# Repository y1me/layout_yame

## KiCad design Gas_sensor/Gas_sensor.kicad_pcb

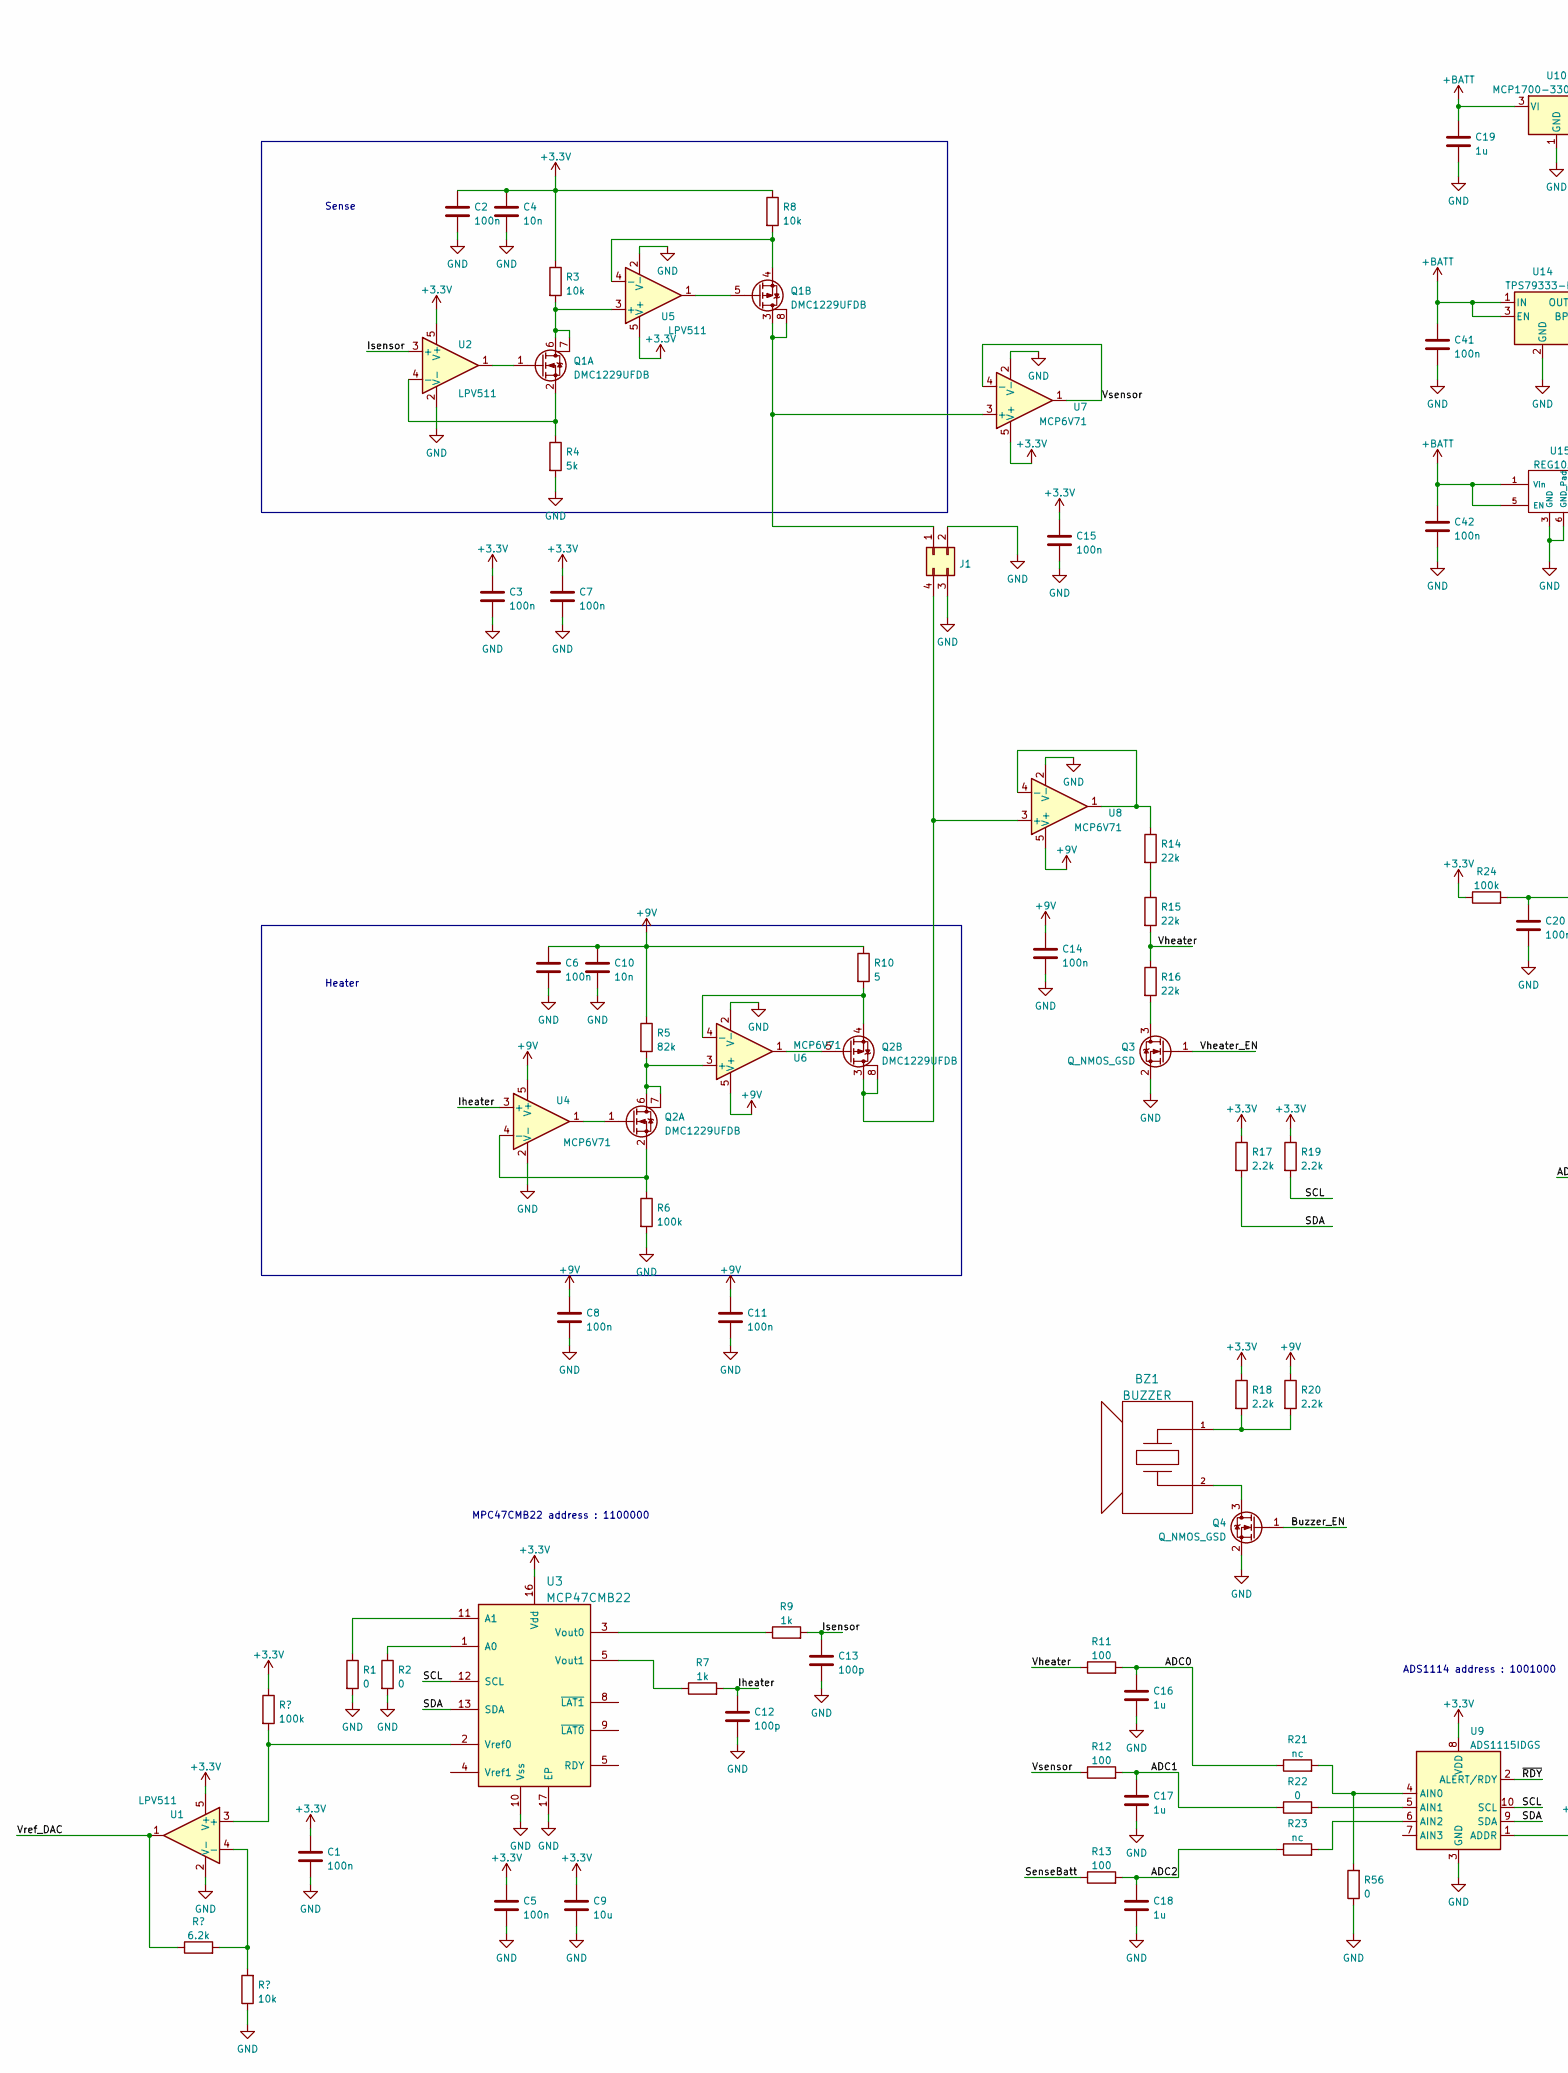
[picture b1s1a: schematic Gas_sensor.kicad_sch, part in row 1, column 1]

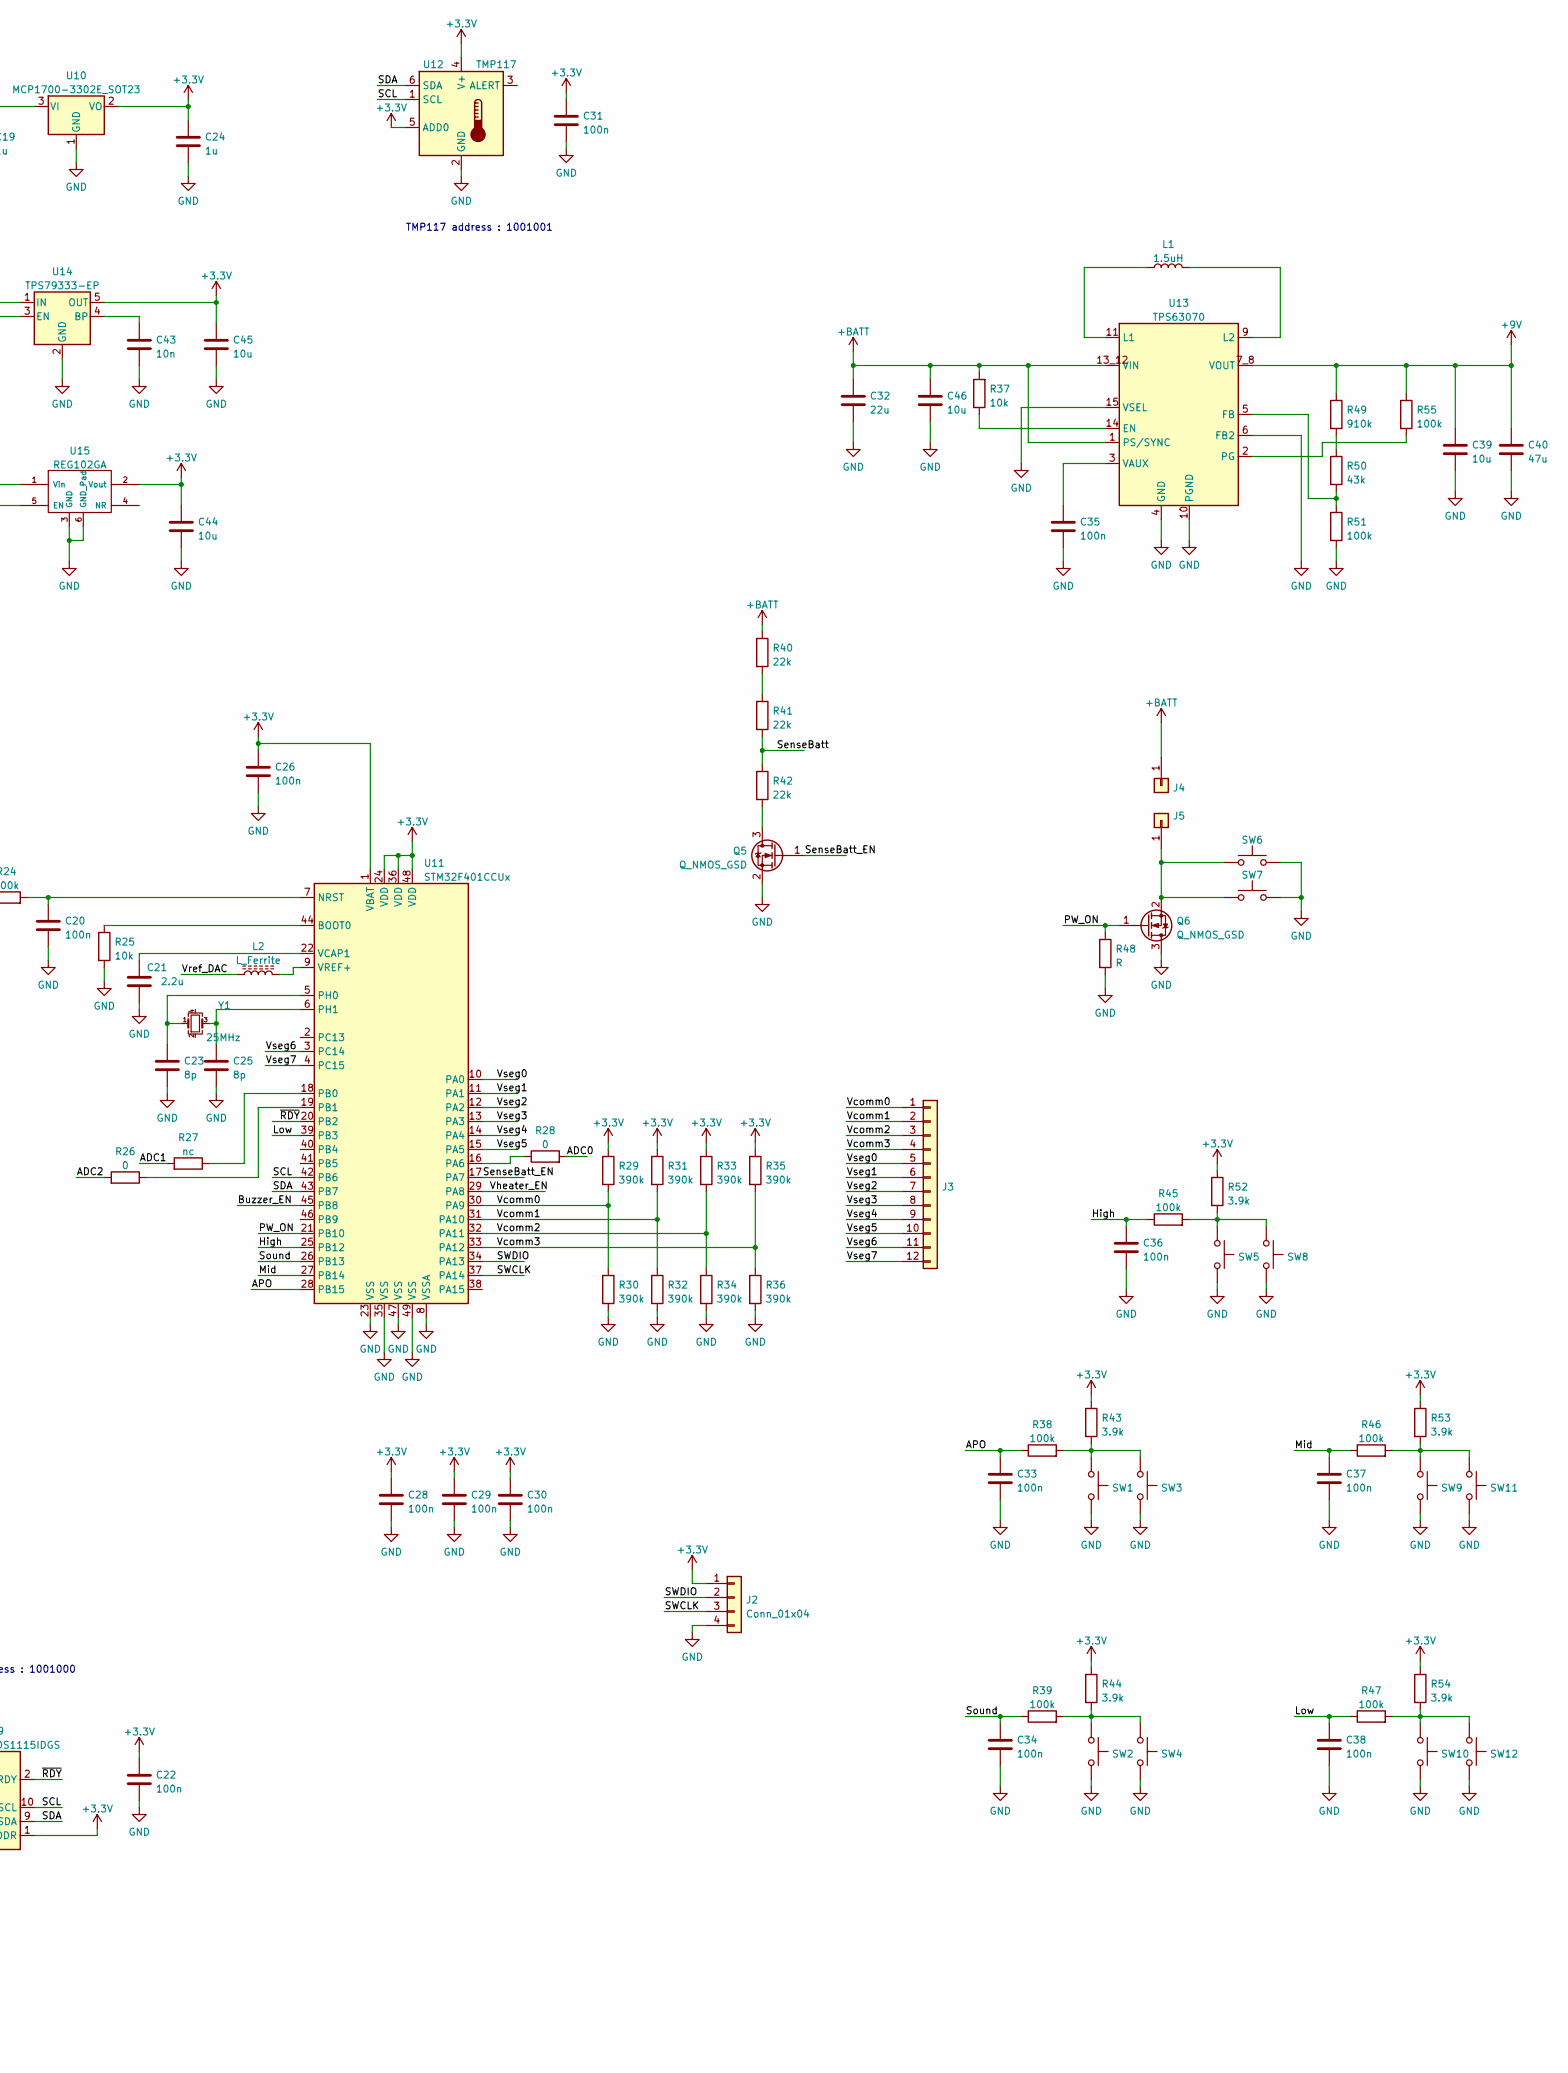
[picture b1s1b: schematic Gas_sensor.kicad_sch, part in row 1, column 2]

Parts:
BZ1: BUZZER; Buzzer_15x7.5RM7.6
C1, C2, C3, C5, C6, C7, C8, C11, C14, C15, C20, C22, C26, C28, C29, C30, C31, C33, C34, C35, C36, C37, C38, C41, C42: 100n; SM0201-MR
C4, C10, C43: 10n; SM0402-MR
C9, C39, C44, C45, C46: 10u; SM0603-MR
C12, C13: 100p; SM0402-MR
C16, C17, C18: 1u; SM0402-MR
C19, C24: 1u; SM0603-MR
C21: 2.2u; SM0603-MR
C23, C25: 8p; SM0402-MR
C32: 22u; SM0603-MR
C40: 47u; SM0805-MR
J1: Conn_02x02_Counter_Clockwise; PinHeader_1x04_P2.54mm_Vertical
J2: Conn_01x04; PinHeader_1x04_P2.54mm_Vertical
J3: Conn_01x10; LCD_Contact_1x12_P2.54mm
J4, J5: Conn_01x01; Conn1_batt
L1: 1.5uH; L_Bourns-SDR0805_7.8x8mm
L2: L_Ferrite; SM0603-MR
Q1, Q2: DMC1229UFDB; U-DFN2020-6_2x2mm_P0.65mm_EP0.6mm
Q3, Q4, Q5, Q6: Q_NMOS_GSD; SOT-23
R1, R2: 0; SM0201-MR
R3, R8, R25, R37: 10k; SM0402-MR
R4: 5k; SM0402-MR
R5: 82k; SM0402-MR
R6, R38, R39, R45, R46, R47, R51, R55: 100k; SM0402-MR
R7, R9: 1k; SM0402-MR
R10: 5; SM0402-MR
R11, R12, R13: 100; SM0402-MR
R14, R15, R16, R40, R41, R42: 22k; SM0402-MR
R17, R19: 2.2k; SM0201-MR
R18, R20: 2.2k; SM0402-MR
R21, R23, R27: nc; SM0402-MR
R22, R26, R28, R56: 0; SM0402-MR
R24: 100k; SM0201-MR
R29, R30, R31, R32, R33, R34, R35, R36: 390k; SM0402-MR
R43, R44, R52, R53, R54: 3.9k; SM0402-MR
R48: R; SM0402-MR
R49: 910k; SM0402-MR
R50: 43k; SM0402-MR
SW1, SW2, SW5, SW7, SW9, SW10: SW_Push; SW_SPST_EVPBF
SW3, SW4, SW6, SW8, SW11, SW12: SW_Push; SW_CARBON
U1, U2, U5: LPV511; SOT-353_SC-70-5
U3: MCP47CMB22; QFN-16-1EP_3x3mm_P0.5mm_EP1.7x1.7mm
U4, U6, U7, U8: MCP6V71; SOT-23-5
U9: ADS1115IDGS; TSSOP-10_3x3mm_P0.5mm
U10: MCP1700-3302E_SOT23; SOT-23
U11: STM32F401CCUx; QFN-48-1EP_7x7mm_P0.5mm_EP5.6x5.6mm
U12: TMP117; WSON-6-1EP_2x2mm_P0.65mm_EP1x1.6mm_ThermalVias
U13: TPS63070; VQFN-HR-15-1EP_3x2.5mm_P0.5m
U14: TPS79333-EP; SOT-23-5
U15: REG102GA; SOT-223-6
Y1: 25MHz; Crystal_SMD_3225-4Pin_3.2x2.5mm

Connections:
+3V3: C1.1, C2.1, C3.1, C4.1, C5.1, C7.1, C9.1, C15.1, C22.1, C24.1, C26.1, C28.1, C29.1, C30.1, C31.1, C44.1, C45.1, J2.1, R3.1, R8.1, R17.1, R18.1, R19.1, R24.1, R29.1, R31.1, R33.1, R35.1, R43.1, R44.1, R52.1, R53.1, R54.1, U1.5 (V+), U2.5 (V+), U3.16 (Vdd), U5.5 (V+), U7.5 (V+), U9.1 (ADDR), U9.8 (VDD), U10.2 (VO), U11.1 (VBAT), U11.24 (VDD), U11.36 (VDD), U11.48 (VDD), U12.4 (V+), U12.5 (ADD0), U14.5 (OUT), U15.2 (Vout)
+9V: C6.1, C8.1, C10.1, C11.1, C14.1, C39.1, C40.1, R5.1, R10.1, R20.1, R49.1, R55.1, U4.5 (V+), U6.5 (V+), U8.5 (V+), U13.7_8 (VOUT)
+BATT: C19.1, C32.1, C41.1, C42.1, C46.1, J4.1, R37.2, R40.1, U10.3 (VI), U13.1 (PS/SYNC), U13.13_12 (VIN), U14.1 (IN), U14.3 (EN), U15.1 (Vin), U15.5 (EN)
/ADC0: C16.1, R11.2, R21.1, R28.2
/ADC1: C17.1, R12.2, R22.1, R27.2
/ADC2: C18.1, R13.2, R23.1, R26.2
/APO: C33.1, R38.1, U11.28 (PB15)
/Buzzer_EN: Q4.1 (G), U11.45 (PB8)
/High: C36.1, R45.1, U11.25 (PB12)
/Iheater: C12.1, R7.2, U4.3 (+)
/Isensor: C13.1, R9.2, U2.3 (+)
/Low: C38.1, R47.1, U11.39 (PB3)
/Mid: C37.1, R46.1, U11.27 (PB14)
/PW_ON: Q6.1 (G), R48.1, U11.21 (PB10)
/SCL: R19.2, U3.12 (SCL), U9.10 (SCL), U11.42 (PB6), U12.1 (SCL)
/SDA: R17.2, U3.13 (SDA), U9.9 (SDA), U11.43 (PB7), U12.6 (SDA)
/SWCLK: J2.3, U11.37 (PA14)
/SWDIO: J2.2, U11.34 (PA13)
/SenseBatt: R13.1, R41.2, R42.1
/SenseBatt_EN: Q5.1 (G), U11.17 (PA7)
/Sound: C34.1, R39.1, U11.26 (PB13)
/Vcomm0: J3.1, R29.2, R30.1, U11.30 (PA9)
/Vcomm1: J3.2, R31.2, R32.1, U11.31 (PA10)
/Vcomm2: J3.3, R33.2, R34.1, U11.32 (PA11)
/Vcomm3: J3.4, R35.2, R36.1, U11.33 (PA12)
/Vheater: R11.1, R15.2, R16.1
/Vheater_EN: Q3.1 (G), U11.29 (PA8)
/Vref_DAC: L2.1, U1.1, U1.4 (-)
/Vseg0: J3.5, U11.10 (PA0)
/Vseg1: J3.6, U11.11 (PA1)
/Vseg2: J3.7, U11.12 (PA2)
/Vseg3: J3.8, U11.13 (PA3)
/Vseg4: J3.9, U11.14 (PA4)
/Vseg5: J3.10, U11.15 (PA5)
/Vseg6: J3.11, U11.3 (PC14)
/Vseg7: J3.12, U11.4 (PC15)
/Vsensor: R12.1, U7.1, U7.4 (-)
/~RDY: U9.2 (ALERT/RDY), U11.20 (PB2)
GND: C1.2, C2.2, C3.2, C4.2, C5.2, C6.2, C7.2, C8.2, C9.2, C10.2, C11.2, C12.2, C13.2, C14.2, C15.2, C16.2, C17.2, C18.2, C19.2, C20.2, C21.2, C22.2, C23.2, C24.2, C25.2, C26.2, C28.2, C29.2, C30.2, C31.2, C32.2, C33.2, C34.2, C35.2, C36.2, C37.2, C38.2, C39.2, C40.2, C41.2, C42.2, C43.2, C44.2, C45.2, C46.2, J1.2, J1.3, J2.4, Q3.2 (S), Q4.2 (S), Q5.2 (S), Q6.3 (D), R1.2, R2.2, R4.2, R6.2, R25.2, R30.2, R32.2, R34.2, R36.2, R48.2, R51.2, R56.1, SW1.2, SW2.2, SW3.2, SW4.2, SW5.2, SW6.2, SW7.2, SW8.2, SW9.2, SW10.2, SW11.2, SW12.2, U1.2 (V-), U2.2 (V-), U3.10 (Vss), U3.17 (EP), U4.2 (V-), U5.2 (V-), U6.2 (V-), U7.2 (V-), U8.2 (V-), U9.3 (GND), U10.1 (GND), U11.8 (VSSA), U11.23 (VSS), U11.35 (VSS), U11.47 (VSS), U11.49 (VSS), U12.2 (GND), U13.4 (GND), U13.6 (FB2), U13.10 (PGND), U13.15 (VSEL), U14.2 (GND), U15.3 (GND), U15.6 (GND_Pad)
unnamed: BZ1.1, R18.2, R20.2
unnamed: BZ1.2, Q4.3 (D)
unnamed: C20.1, R24.2, U11.7 (NRST)
unnamed: C21.1, U11.22 (VCAP1)
unnamed: C23.1, U11.5 (PH0), Y1.1
unnamed: C25.1, U11.6 (PH1), Y1.3
unnamed: C35.1, U13.3 (VAUX)
unnamed: C43.1, U14.4 (BP)
unnamed: J1.1, Q1.3 (D2), Q1.8 (D2), U7.3 (+)
unnamed: J1.4, Q2.3 (D2), Q2.8 (D2), U8.3 (+)
unnamed: J5.1, Q6.2 (S), SW6.1, SW7.1
unnamed: L1.1, U13.11 (L1)
unnamed: L1.2, U13.9 (L2)
unnamed: L2.2, U11.9 (VREF+)
unnamed: Q1.1 (G1), U2.1
unnamed: Q1.2 (S1), R4.1, U2.4 (-)
unnamed: Q1.4 (S2), R8.2, U5.4 (-)
unnamed: Q1.5 (G2), U5.1
unnamed: Q1.6 (D1), Q1.7 (D1), R3.2, U5.3 (+)
unnamed: Q2.1 (G1), U4.1
unnamed: Q2.2 (S1), R6.1, U4.4 (-)
unnamed: Q2.4 (S2), R10.2, U6.4 (-)
unnamed: Q2.5 (G2), U6.1
unnamed: Q2.6 (D1), Q2.7 (D1), R5.2, U6.3 (+)
unnamed: Q3.3 (D), R16.2
unnamed: Q5.3 (D), R42.2
unnamed: R1.1, U3.11 (A1)
unnamed: R2.1, U3.1 (A0)
unnamed: R7.1, U3.5 (Vout1)
unnamed: R9.1, U3.3 (Vout0)
unnamed: R14.1, U8.1, U8.4 (-)
unnamed: R14.2, R15.1
unnamed: R21.2, R56.2, U9.4 (AIN0)
unnamed: R22.2, U9.5 (AIN1)
unnamed: R23.2, U9.6 (AIN2)
unnamed: R25.1, U11.44 (BOOT0)
unnamed: R26.1, U11.19 (PB1)
unnamed: R27.1, U11.18 (PB0)
unnamed: R28.1, U11.16 (PA6)
unnamed: R37.1, U13.14 (EN)
unnamed: R38.2, R43.2, SW1.1, SW3.1
unnamed: R39.2, R44.2, SW2.1, SW4.1
unnamed: R40.2, R41.1
unnamed: R45.2, R52.2, SW5.1, SW8.1
unnamed: R46.2, R53.2, SW9.1, SW11.1
unnamed: R47.2, R54.2, SW10.1, SW12.1
unnamed: R49.2, R50.1
unnamed: R50.2, R51.1, U13.5 (FB)
unnamed: R55.2, U13.2 (PG)
unnamed: U1.3 (+), U3.2 (Vref0)

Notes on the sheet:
MPC47CMB22 address : 1100000
Sense
Heater
TMP117 address : 1001001
ADS1114 address : 1001000

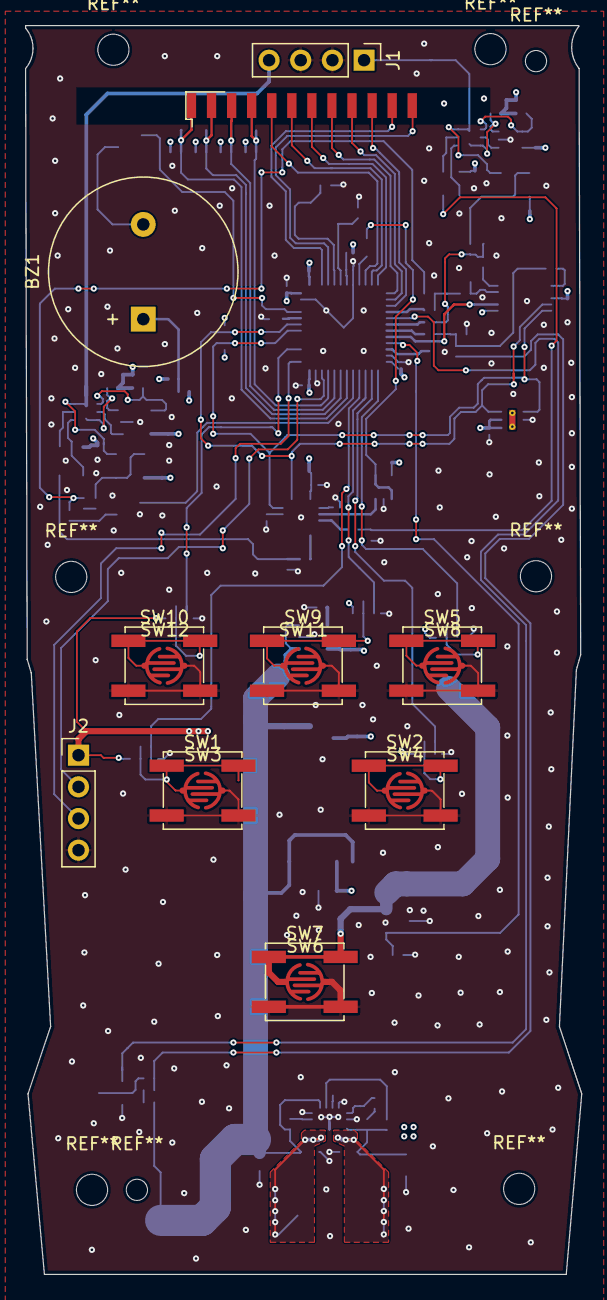
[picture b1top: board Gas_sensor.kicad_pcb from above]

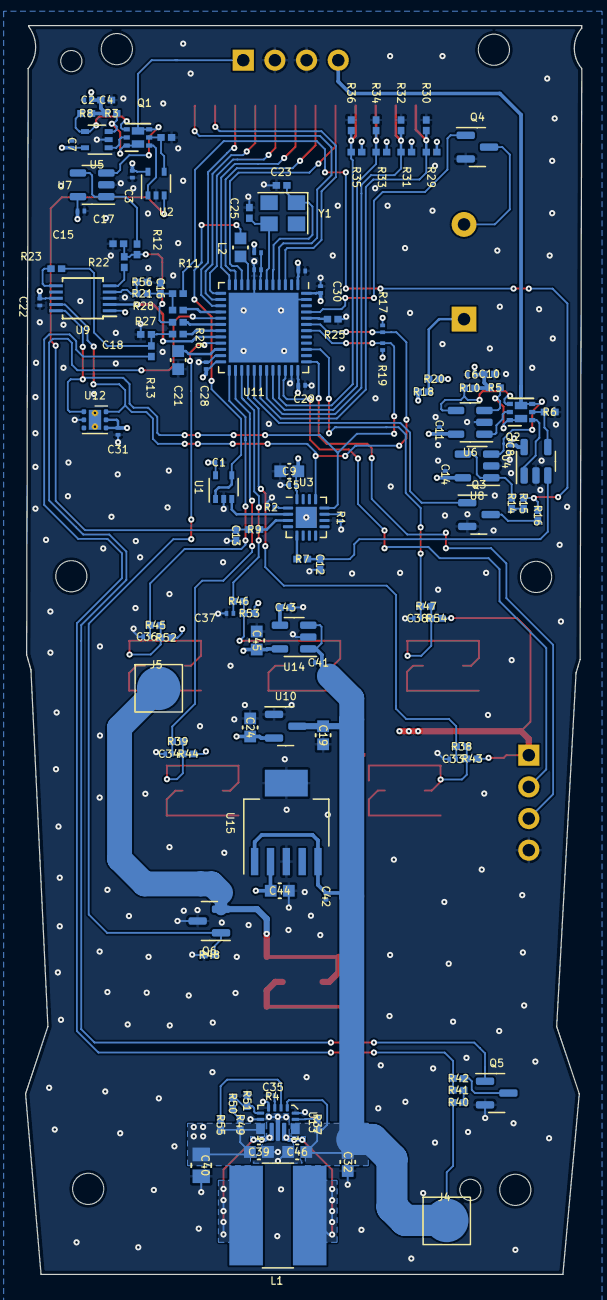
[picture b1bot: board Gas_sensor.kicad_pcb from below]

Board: 4 copper layers, 44.6 x 100.2 mm, 143 parts (127 on the bottom side), 89 nets.

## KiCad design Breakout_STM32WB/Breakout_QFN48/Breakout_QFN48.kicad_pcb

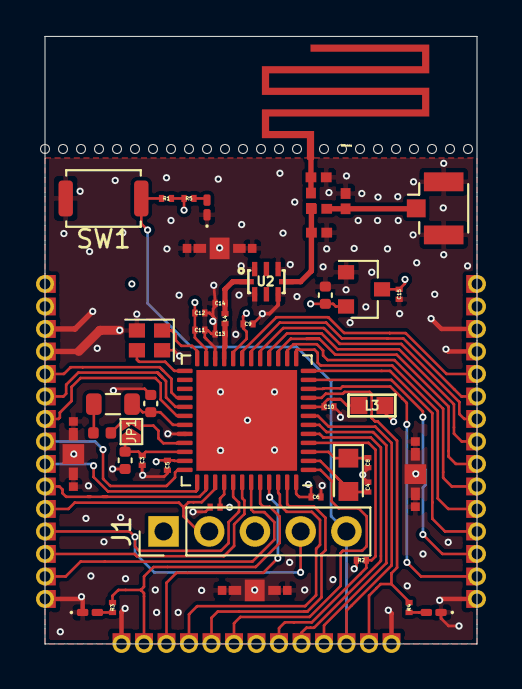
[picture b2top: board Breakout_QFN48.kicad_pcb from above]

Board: 4 copper layers, 24.0 x 33.8 mm, 114 parts (0 on the bottom side), 50 nets.

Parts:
AE1: Antenna; PCB_Ant_2.4GHz_1
C1, C7, C19: 4.7u; C_0402_1005Metric
C2, C3, C5, C6, C9, C10, C12: 100n; SM0201-MR
C4, C8: 10p; SM0201-MR
C11: 100p; SM0201-MR
C13: 0.8pF; SM0201-MR
C14: 0.3pF; SM0201-MR
C15: 1u; SM0201-MR
C17, C18, C20: C; SM0402-MR
D1, D2, D3: IN-S21AT2B; LED_0201_0603Metric_Pad0.64x0.40mm_HandSolder
Hole_0.5mm, Hole_0.5mm#2, Hole_0.5mm#3, Hole_0.5mm#4, Hole_0.5mm#5, Hole_0.5mm#6, Hole_0.5mm#7, Hole_0.5mm#8, Hole_0.5mm#9, Hole_0.5mm#10, Hole_0.5mm#11, Hole_0.5mm#12, Hole_0.5mm#13, Hole_0.5mm#14, Hole_0.5mm#15, Hole_0.5mm#16, Hole_0.5mm#17, Hole_0.5mm#18, Hole_0.5mm#19, Hole_0.5mm#20, Hole_0.5mm#21, Hole_0.5mm#22, Hole_0.5mm#23, Hole_0.5mm#24: VAL**; Hole_0.5mm
J1: Debug conn; PinHeader_1x05_P2.54mm_Vertical
J2, J3, J4, J5, J6, J7, J8, J9, J10, J11, J12, J13, J14, J15, J16, J17, J18, J19, J20, J21, J22, J23, J24, J25, J26, J27, J28, J29, J30, J31, J32, J33, J34, J35, J36, J37, J38, J39, J40, J41, J42, J43, J44: Conn_01x01; Castellated
J45, J46, J47, J48: Conn_01x01; S0951-46R
JP1: Jumper_2_Open; SolderJumper-2_Open_TrianglePad1.0x1.0mm
L1: 10uH; L_0805_2012Metric
L2: 10nH; L_0402_1005Metric
L3: BK1608TS601-T; SM0603-MR
L4: 2.7nH; SM0201-MR
L5, L6: L; SM0402-MR
R1, R2: 100k; SM0201-MR
R3, R4, R5: 1k; SM0201-MR
RF_J1: UFL; U.FL_Hirose_U.FL-R-SMT-1_Vertical
SW1: Reset; SW_Push_SPST_NO_Alps_SKRK
U1: STM32WB55Cx; QFN-48-1EP_7x7mm_P0.5mm_EP5.6x5.6mm
U2: LFL212G45TC1A007; LFL21_TC_(0805)_Series
U3: MCP1700-3302E_SOT23; SOT-23
Y1: NX2012SA_32-768kHz; Crystal_SMD_2012-2Pin_2.0x1.2mm_HandSoldering
Y2: NX2016_32M; Crystal_SMD_2016-4Pin_2.0x1.6mm

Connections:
+3V3: C2.1, C5.1, C6.1, C9.1, C11.1, C12.1, C19.1, J1.1, J36.1, J38.1, L3.2, R1.1, R5.1, U1.20, U1.23, U1.35, U1.40, U1.48, U3.2
+5V: C15.1, J35.1, J37.1, U3.3
/BOOT0: J3.1, R2.2, U1.4
/LED1: J22.1, R3.1, U1.44
/LED2: J4.1, R4.1, U1.9
/NRST: J1.5, J30.1, R1.2, SW1.1, U1.7
/SWDCLK: J1.4, J40.1, U1.41
/SWDIO: J1.2, J39.1, U1.39
GND: C1.2, C2.2, C3.2, C4.2, C5.2, C6.2, C7.2, C8.2, C9.2, C10.2, C11.2, C12.2, C13.2, C14.2, C15.2, C17.2, C18.2, C19.2, C20.2, D1.1, D2.1, D3.1, J1.3, J29.1, J31.1, J32.1, J33.1, J34.1, J41.1, J42.1, J43.1, J44.1, J45.1, J46.1, J47.1, J48.1, R2.1, RF_J1.2, SW1.2, U1.22, U1.32, U1.49, U2.1, U2.3, U2.5, U2.7, U3.1, Y2.2, Y2.4
unnamed: AE1.1, C18.1, L5.2
unnamed: C1.1, C3.1, JP1.1, U1.34
unnamed: C4.1, U1.2, Y1.2
unnamed: C7.1, L1.1, U1.31
unnamed: C8.1, U1.3, Y1.1
unnamed: C10.1, L3.1, U1.8
unnamed: C13.1, L4.1, U1.21
unnamed: C14.1, L4.2, U2.8
unnamed: C17.1, L5.1, L6.1, U2.4
unnamed: C20.1, L6.2, RF_J1.1
unnamed: D1.2, R3.2
unnamed: D2.2, R4.2
unnamed: D3.2, R5.2
unnamed: J2.1, U1.1
unnamed: J5.1, U1.10
unnamed: J6.1, U1.11
unnamed: J7.1, U1.12
unnamed: J8.1, U1.13
unnamed: J9.1, U1.14
unnamed: J10.1, U1.15
unnamed: J11.1, U1.16
unnamed: J12.1, U1.17
unnamed: J13.1, U1.18
unnamed: J14.1, U1.36
unnamed: J15.1, U1.37
unnamed: J16.1, U1.38
unnamed: J17.1, U1.42
unnamed: J18.1, U1.28
unnamed: J19.1, U1.29
unnamed: J20.1, U1.19
unnamed: J21.1, U1.43
unnamed: J23.1, U1.45
unnamed: J24.1, U1.46
unnamed: J25.1, U1.47
unnamed: J26.1, U1.5
unnamed: J27.1, U1.6
unnamed: J28.1, U1.30
unnamed: JP1.2, L2.2, U1.33
unnamed: L1.2, L2.1
unnamed: U1.24, Y2.1
unnamed: U1.25, Y2.3

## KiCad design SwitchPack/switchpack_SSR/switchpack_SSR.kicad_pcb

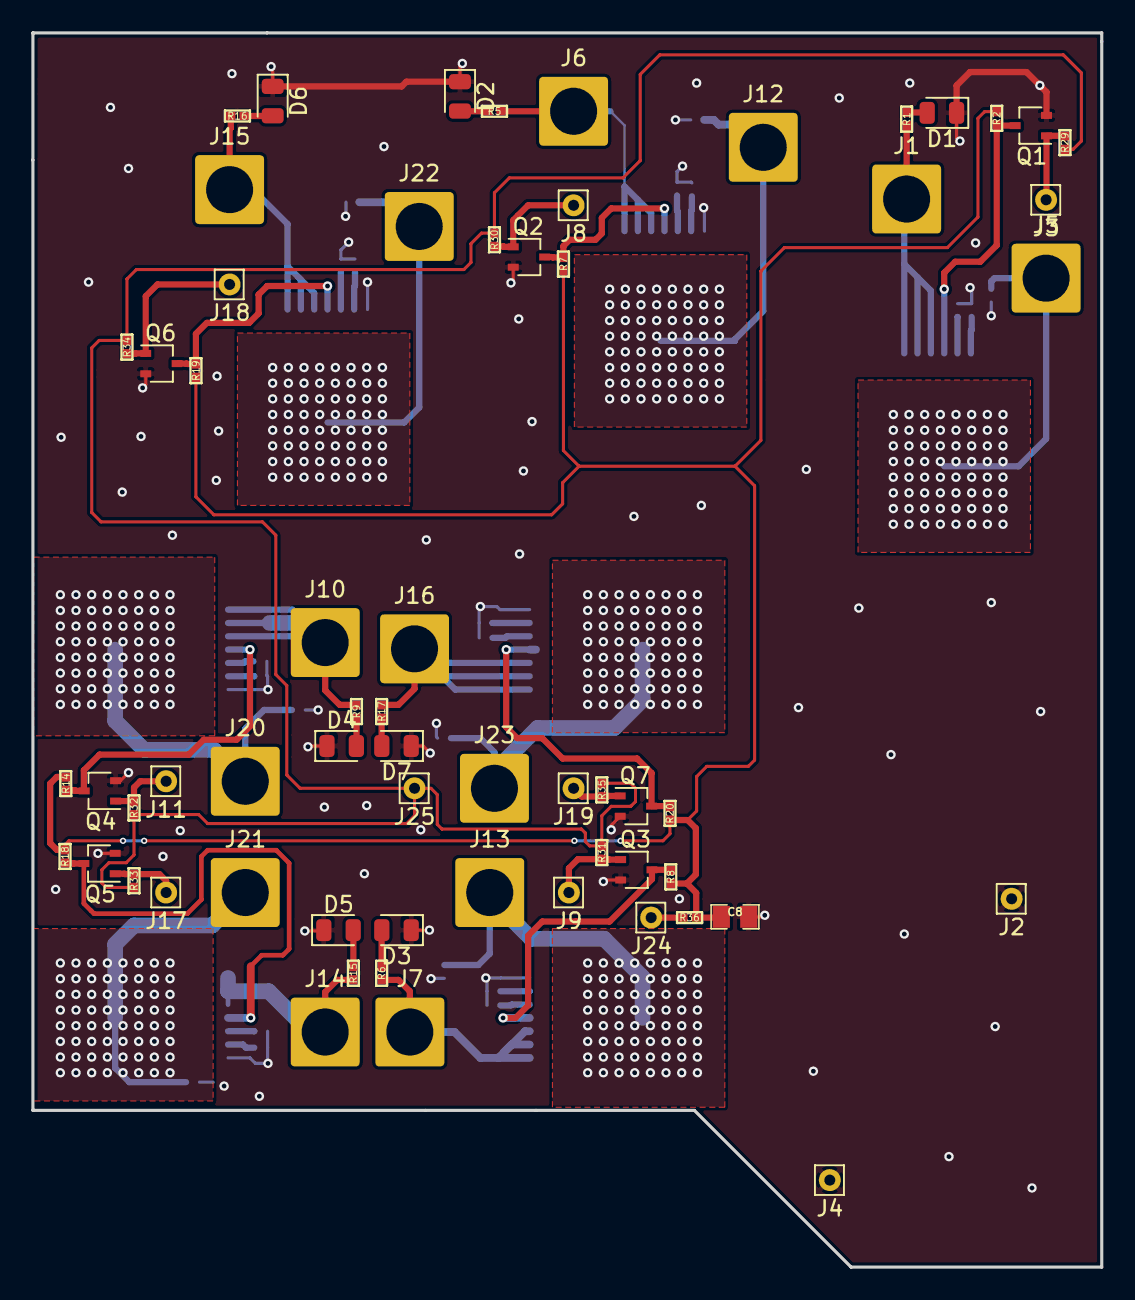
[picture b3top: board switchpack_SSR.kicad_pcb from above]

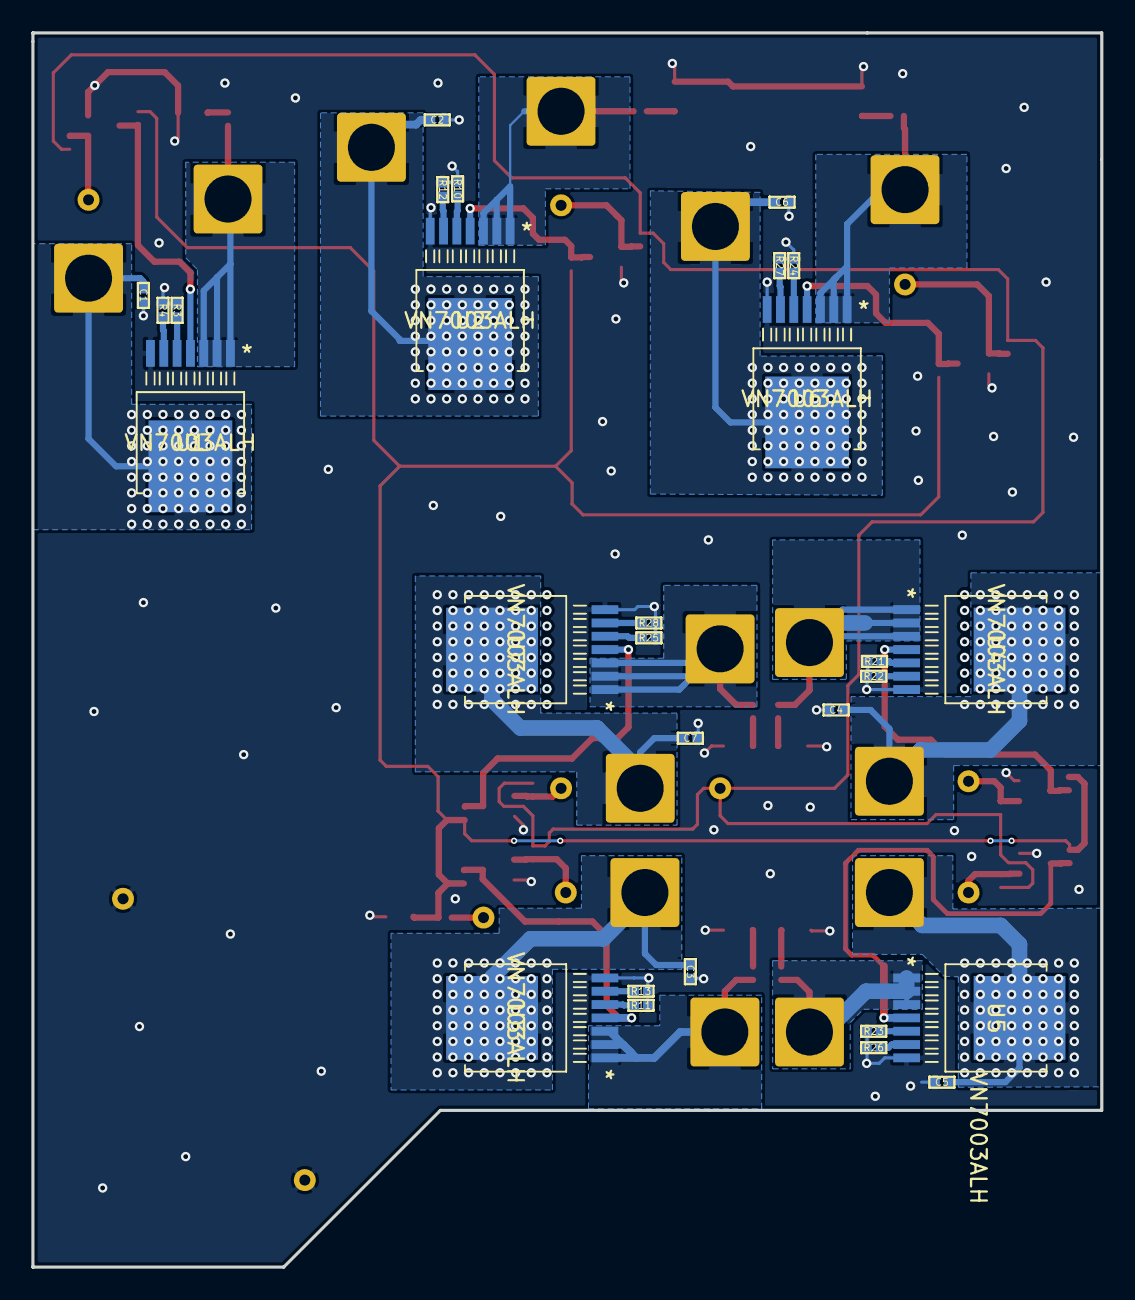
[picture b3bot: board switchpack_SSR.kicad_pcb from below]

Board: 2 copper layers, 68.2 x 78.8 mm, 90 parts (28 on the bottom side), 53 nets.

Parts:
C1, C2, C3, C4, C5, C6, C7: 100n; SM0402-MR
C8: 22u; SM0805-MR
D1, D2, D3, D4, D5, D6, D7: LED; LED_0805_2012Metric
J1: OUT_DIP_LEFT; SolderWire-2.5sqmm_1x01_D2.4mm_OD4.4mm
J2, J4: GND; Pin_D0.7mm_L6.5mm_W1.8mm_FlatFork
J3: IN_DIP_LEFT; Pin_D0.7mm_L6.5mm_W1.8mm_FlatFork
J5: VBAT_DIP_LEFT; SolderWire-2.5sqmm_1x01_D2.4mm_OD4.4mm
J6: OUT_MB_LEFT; SolderWire-2.5sqmm_1x01_D2.4mm_OD4.4mm
J7: OUT_PARKING_LIGHT; SolderWire-2.5sqmm_1x01_D2.4mm_OD4.4mm
J8: IN_MB_LEFT; Pin_D0.7mm_L6.5mm_W1.8mm_FlatFork
J9: IN_PARKING_LIGHT; Pin_D0.7mm_L6.5mm_W1.8mm_FlatFork
J10: OUT_AC_REC; SolderWire-2.5sqmm_1x01_D2.4mm_OD4.4mm
J11: IN_AC_REC; Pin_D0.7mm_L6.5mm_W1.8mm_FlatFork
J12: VBAT_MB_LEFT; SolderWire-2.5sqmm_1x01_D2.4mm_OD4.4mm
J13: VBAT_PARKING_LIGHT; SolderWire-2.5sqmm_1x01_D2.4mm_OD4.4mm
J14: OUT_DIP_RIGHT; SolderWire-2.5sqmm_1x01_D2.4mm_OD4.4mm
J15: OUT_MB_RIGHT; SolderWire-2.5sqmm_1x01_D2.4mm_OD4.4mm
J16: OUT_FOG_LIGHT; SolderWire-2.5sqmm_1x01_D2.4mm_OD4.4mm
J17: IN_DIP_RIGHT; Pin_D0.7mm_L6.5mm_W1.8mm_FlatFork
J18: IN_MB_RIGHT; Pin_D0.7mm_L6.5mm_W1.8mm_FlatFork
J19: IN_FOG_LIGHT; Pin_D0.7mm_L6.5mm_W1.8mm_FlatFork
J20: VBAT_AC_REC; SolderWire-2.5sqmm_1x01_D2.4mm_OD4.4mm
J21: VBAT_DIP_RIGHT; SolderWire-2.5sqmm_1x01_D2.4mm_OD4.4mm
J22: VBAT_MB_RIGHT; SolderWire-2.5sqmm_1x01_D2.4mm_OD4.4mm
J23: VBAT_FOG_LIGHT; SolderWire-2.5sqmm_1x01_D2.4mm_OD4.4mm
J24: +3.3V; Pin_D0.7mm_L6.5mm_W1.8mm_FlatFork
J25: +12V; Pin_D0.7mm_L6.5mm_W1.8mm_FlatFork
Q1, Q2, Q3, Q4, Q5, Q6, Q7: DTC143Z; SOT-323_SC-70
R1, R3, R5, R6, R9, R10, R11, R15, R16, R17, R21, R23, R24, R25: 1k; SM0402-MR
R2, R4, R7, R8, R12, R13, R14, R18, R19, R20, R22, R26, R27, R28, R29, R30, R31, R32, R33, R34, R35: 15k; SM0402-MR
R36: 0R; SM0402-MR
U1, U2, U3, U4, U5, U6, U7: VN7003ALH

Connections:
+3V3: C8.1, R2.2, R7.2, R8.2, R14.2, R18.2, R19.2, R20.2, R36.2
+12V: J25.1, R29.2, R30.2, R31.2, R32.2, R33.2, R34.2, R35.2
GND: C1.2, C2.2, C3.2, C4.2, C5.2, C6.2, C7.2, C8.2, D1.1, D2.1, D3.1, D4.1, D5.1, D6.1, D7.1, J2.1, J4.1, Q1.2, Q2.2, Q3.2, Q4.2, Q5.2, Q6.2, Q7.2, R3.2, R4.2, R10.2, R11.2, R12.2, R13.2, R21.2, R22.2, R23.2, R24.2, R25.2, R26.2, R27.2, R28.2, U1.7, U2.7, U3.7, U4.7, U5.7, U6.7, U7.7
unnamed: C1.1, J5.1, U1.8
unnamed: C2.1, J12.1, U2.8
unnamed: C3.1, J13.1, U3.8
unnamed: C4.1, J20.1, U4.8
unnamed: C5.1, J21.1, U5.8
unnamed: C6.1, J22.1, U6.8
unnamed: C7.1, J23.1, U7.8
unnamed: D1.2, R1.2
unnamed: D2.2, R5.2
unnamed: D3.2, R6.2
unnamed: D4.2, R9.2
unnamed: D5.2, R15.2
unnamed: D6.2, R16.2
unnamed: D7.2, R17.2
unnamed: J1.1, R1.1, U1.1, U1.2, U1.3
unnamed: J3.1, Q1.1, R29.1
unnamed: J6.1, R5.1, U2.1, U2.2, U2.3
unnamed: J7.1, R6.1, U3.1, U3.2, U3.3
unnamed: J8.1, Q2.1, R30.1
unnamed: J9.1, Q3.1, R31.1
unnamed: J10.1, R9.1, U4.1, U4.2, U4.3
unnamed: J11.1, Q4.1, R32.1
unnamed: J14.1, R15.1, U5.1, U5.2, U5.3
unnamed: J15.1, R16.1, U6.1, U6.2, U6.3
unnamed: J16.1, R17.1, U7.1, U7.2, U7.3
unnamed: J17.1, Q5.1, R33.1
unnamed: J18.1, Q6.1, R34.1
unnamed: J19.1, Q7.1, R35.1
unnamed: J24.1, R36.1
unnamed: Q1.3, R2.1, U1.4
unnamed: Q2.3, R7.1, U2.4
unnamed: Q3.3, R8.1, U3.4
unnamed: Q4.3, R14.1, U4.4
unnamed: Q5.3, R18.1, U5.4
unnamed: Q6.3, R19.1, U6.4
unnamed: Q7.3, R20.1, U7.4
unnamed: R3.1, U1.5
unnamed: R4.1, U1.6
unnamed: R10.1, U2.5
unnamed: R11.1, U3.5
unnamed: R12.1, U2.6
unnamed: R13.1, U3.6
unnamed: R21.1, U4.5
unnamed: R22.1, U4.6
unnamed: R23.1, U5.5
unnamed: R24.1, U6.5
unnamed: R25.1, U7.5
unnamed: R26.1, U5.6
unnamed: R27.1, U6.6
unnamed: R28.1, U7.6
